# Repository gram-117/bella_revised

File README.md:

# bella

KICAD files + LTspice simulation for PMT driver circuit
tested and working

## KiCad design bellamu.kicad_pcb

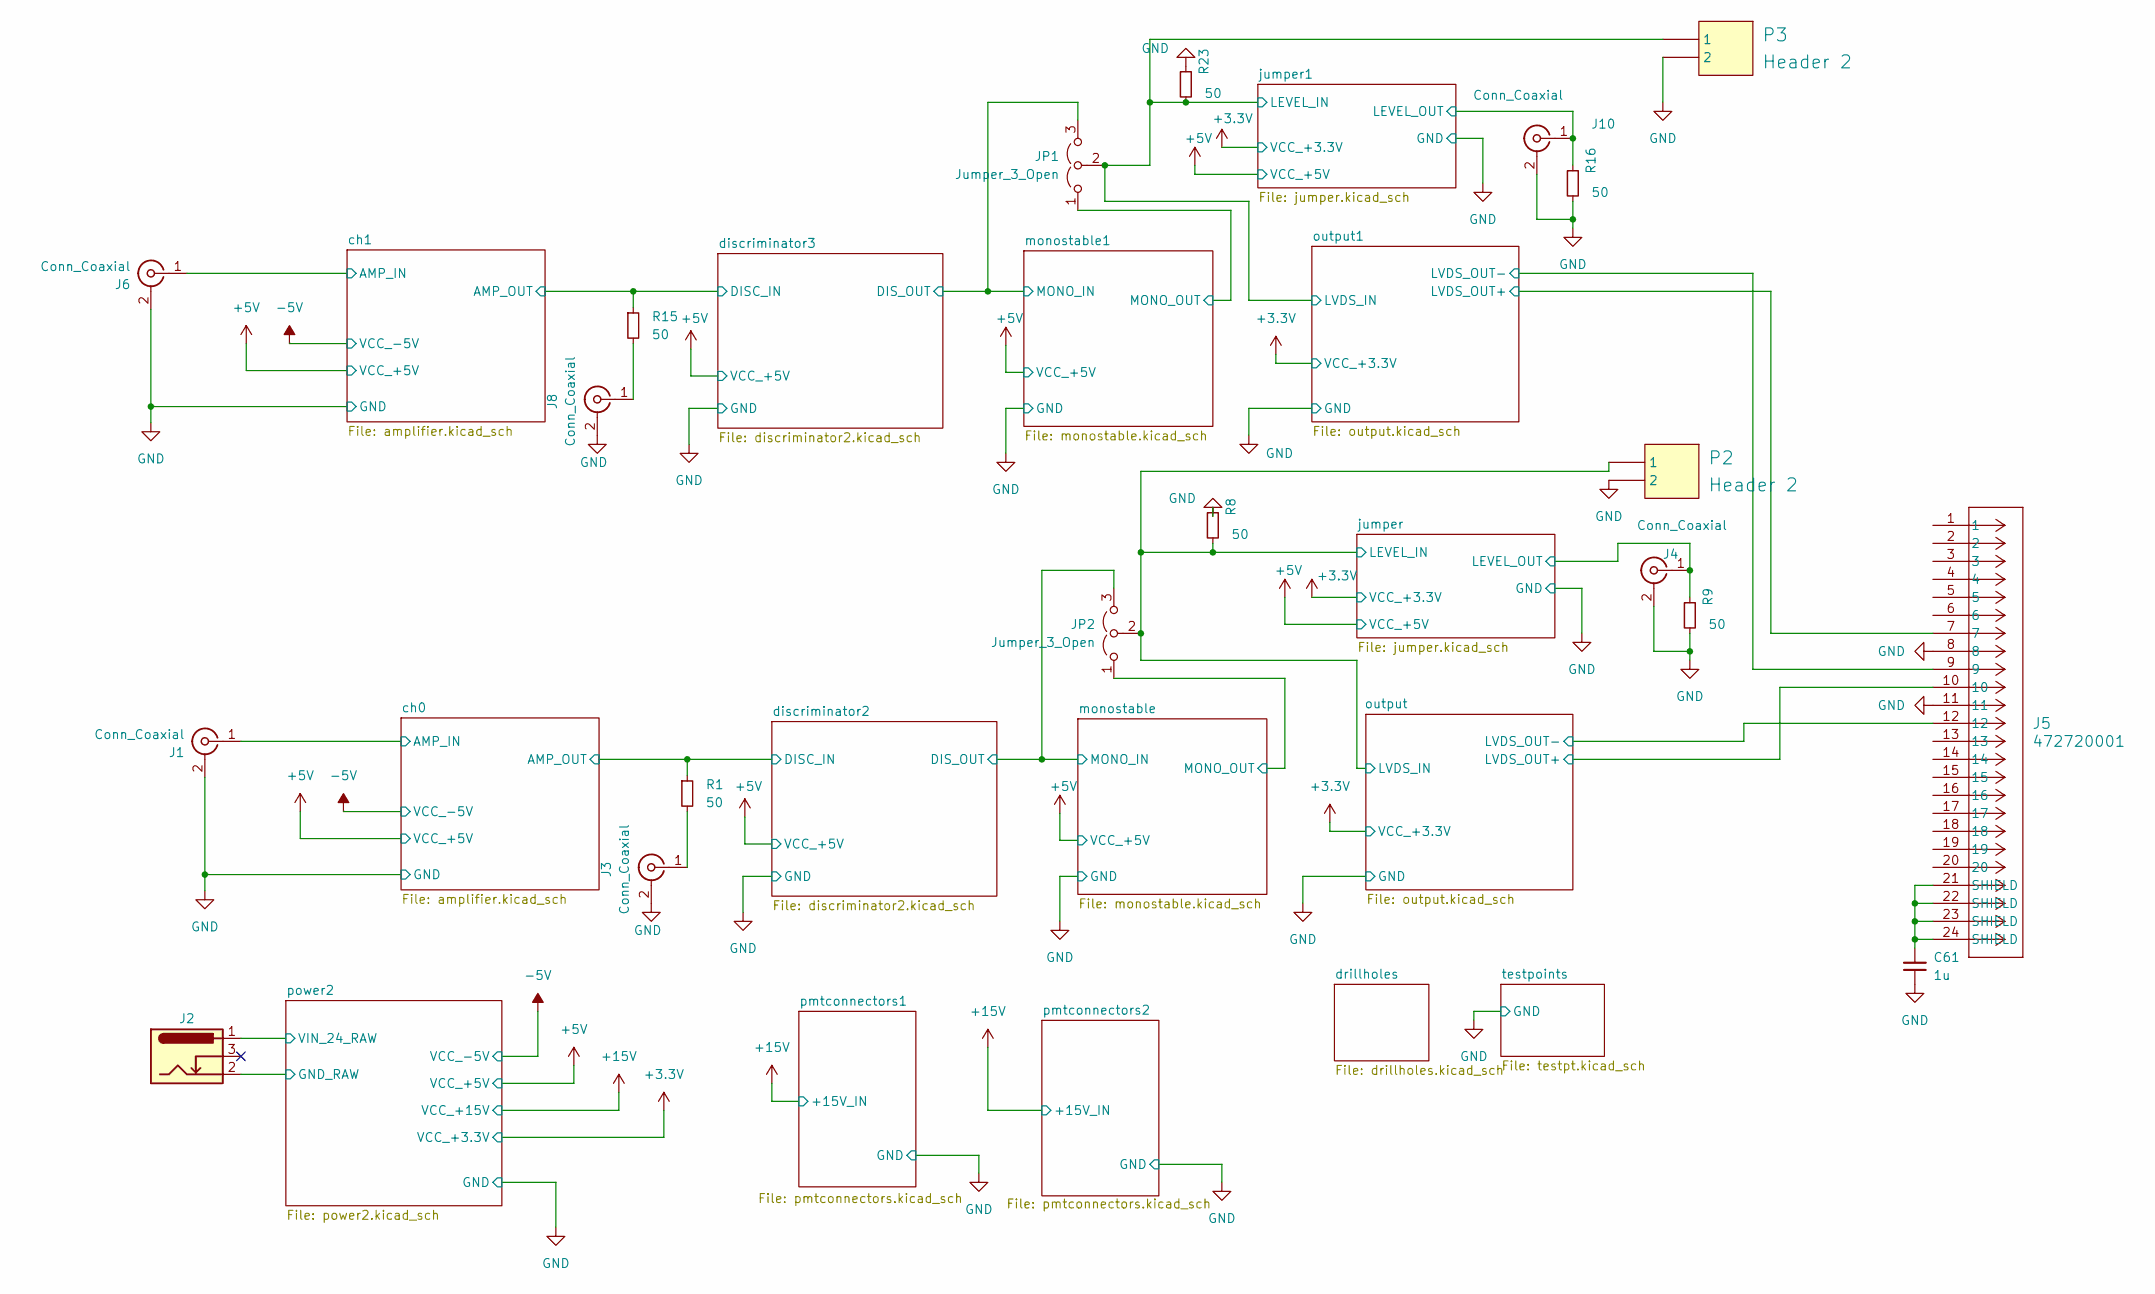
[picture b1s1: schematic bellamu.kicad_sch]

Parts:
C61: 1u; C_0603_1608Metric
J1, J3, J4, J6, J8, J10: Conn_Coaxial; EPB00250NTN
J2: Barrel_Jack_Switch_Pin3Ring; PJ-102AH
J5: 472720001; CONN_47272-0001_MOL
JP1, JP2: Jumper_3_Open; SolderJumper-3_P1.3mm_Open_Pad1.0x1.5mm
P2, P3: Header 2; PinSocket_1x02_P2.54mm_Vertical
R1, R8, R9, R15, R16, R23: 50; R_0805_2012Metric

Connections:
/ch0/AMP_IN: J1.1 (In); also elsewhere on the board
/ch0/AMP_OUT: R1.1; also elsewhere on the board
/ch1/AMP_IN: J6.1 (In); also elsewhere on the board
/ch1/AMP_OUT: R15.1; also elsewhere on the board
/discriminator2/DIS_OUT: JP2.3 (B); also elsewhere on the board
/discriminator3/DIS_OUT: JP1.3 (B); also elsewhere on the board
/jumper1/LEVEL_IN: JP1.2 (C), P3.1, R23.2; also elsewhere on the board
/jumper1/LEVEL_OUT: J10.1 (In), R16.1; also elsewhere on the board
/jumper/LEVEL_IN: JP2.2 (C), P2.1, R8.2; also elsewhere on the board
/jumper/LEVEL_OUT: J4.1 (In), R9.1; also elsewhere on the board
/monostable1/MONO_OUT: JP1.1 (A); also elsewhere on the board
/monostable/MONO_OUT: JP2.1 (A); also elsewhere on the board
/output1/LVDS_OUT+: J5.7; also elsewhere on the board
/output1/LVDS_OUT-: J5.9; also elsewhere on the board
/output/LVDS_OUT+: J5.10; also elsewhere on the board
/output/LVDS_OUT-: J5.12; also elsewhere on the board
/power2/GND_RAW: J2.2; also elsewhere on the board
/power2/VIN_24_RAW: J2.1; also elsewhere on the board
unnamed: C61.2, J5.21 (SHIELD), J5.22 (SHIELD), J5.23 (SHIELD), J5.24 (SHIELD)
unnamed: J3.1 (In), R1.2
unnamed: J8.1 (In), R15.2

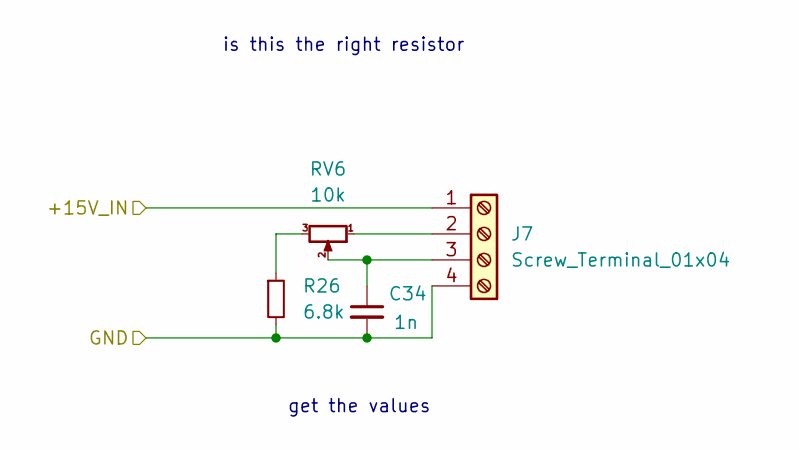
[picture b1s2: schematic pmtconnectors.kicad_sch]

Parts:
C34: 1n; C_0805_2012Metric
J7: Screw_Terminal_01x04; 1725672
R26: 6.8k; R_0805_2012Metric
RV6: 10k; Potentiometer_Bourns_3266W_Vertical

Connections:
+15V: J7.1; also elsewhere on the board
unnamed: J7.2, RV6.1
unnamed: C34.1, J7.3, RV6.2
unnamed: R26.1, RV6.3

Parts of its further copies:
C40: 1n; C_0805_2012Metric
J9: Screw_Terminal_01x04; 1725672
R29: 6.8k; R_0805_2012Metric
RV5: 10k; Potentiometer_Bourns_3266W_Vertical

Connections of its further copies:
+15V: J9.1; also elsewhere on the board
unnamed: J9.2, RV5.1
unnamed: C40.1, J9.3, RV5.2
unnamed: R29.1, RV5.3

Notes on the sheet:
is this the right resistor
get the values

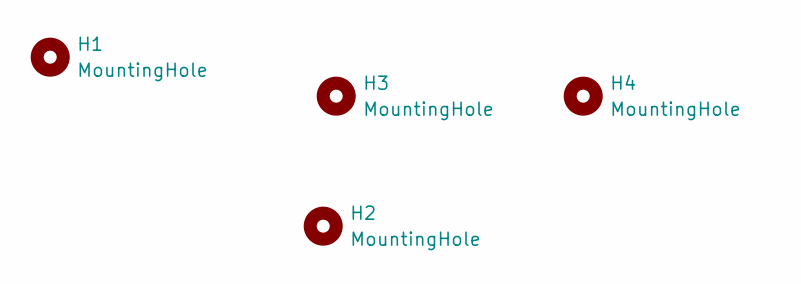
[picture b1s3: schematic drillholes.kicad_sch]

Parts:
H1, H2, H3, H4: MountingHole; MountingHole_2.5mm

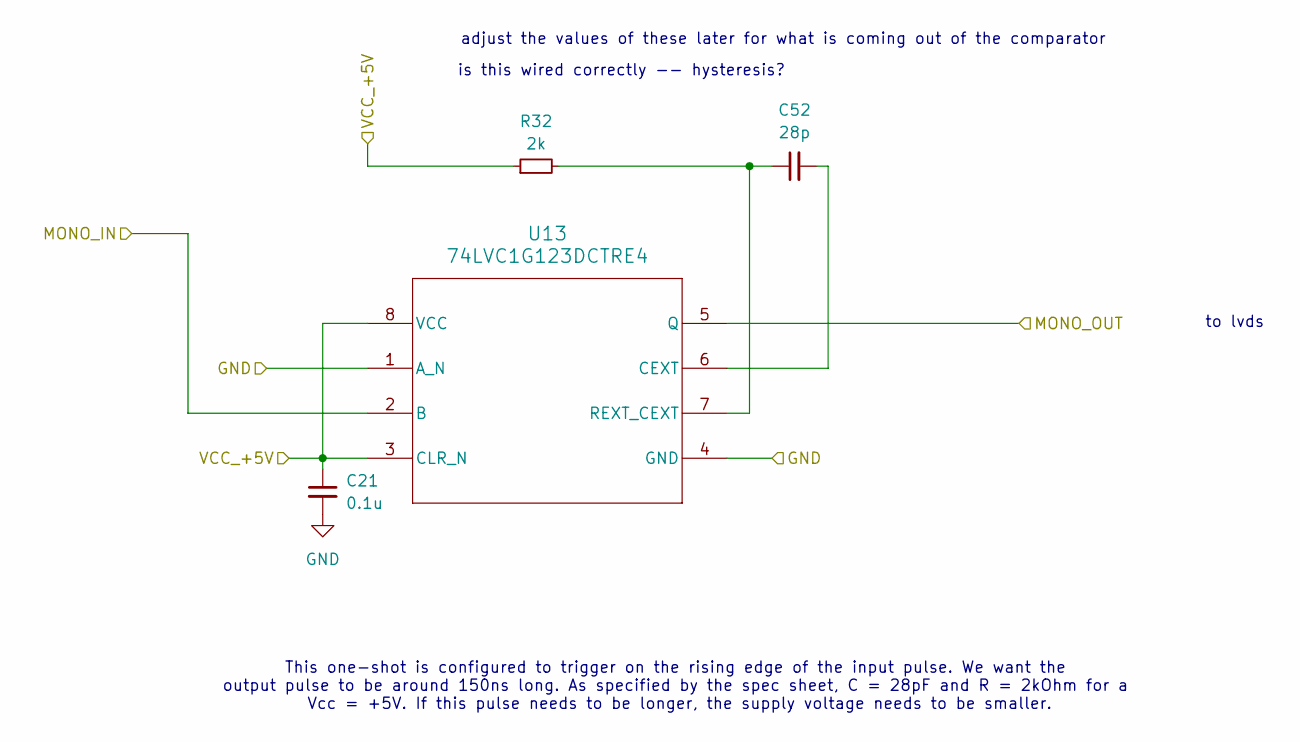
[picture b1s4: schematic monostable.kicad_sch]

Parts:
C21: 0.1u; C_0603_1608Metric
C52: 28p; C_0805_2012Metric
R32: 2k; R_0805_2012Metric
U13: 74LVC1G123DCTRE4; DCT0008A_L

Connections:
+5V: C21.1, R32.1, U13.3 (CLR_N), U13.8 (VCC); also elsewhere on the board
/discriminator2/DIS_OUT: U13.2 (B); also elsewhere on the board
/monostable/MONO_OUT: U13.5 (Q); also elsewhere on the board
unnamed: C52.2, U13.6 (CEXT)
unnamed: C52.1, R32.2, U13.7 (REXT_CEXT)

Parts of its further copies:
C53: 0.1u; C_0603_1608Metric
C54: 28p; C_0805_2012Metric
R33: 2k; R_0805_2012Metric
U15: 74LVC1G123DCTRE4; DCT0008A_L

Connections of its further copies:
+5V: C53.1, R33.1, U15.3 (CLR_N), U15.8 (VCC); also elsewhere on the board
/discriminator3/DIS_OUT: U15.2 (B); also elsewhere on the board
/monostable1/MONO_OUT: U15.5 (Q); also elsewhere on the board
unnamed: C54.2, U15.6 (CEXT)
unnamed: C54.1, R33.2, U15.7 (REXT_CEXT)

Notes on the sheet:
adjust the values of these later for what is coming out of the comparator
This one-shot is configured to trigger on the rising edge of the input pulse. We want the output pulse to be around 150ns long. As specified by the spec sheet, C = 28pF and R = 2kOhm for a Vcc = +5V. If this pulse needs to be longer, the supply voltage needs to be smaller.
is this wired correctly -- hysteresis?
to lvds

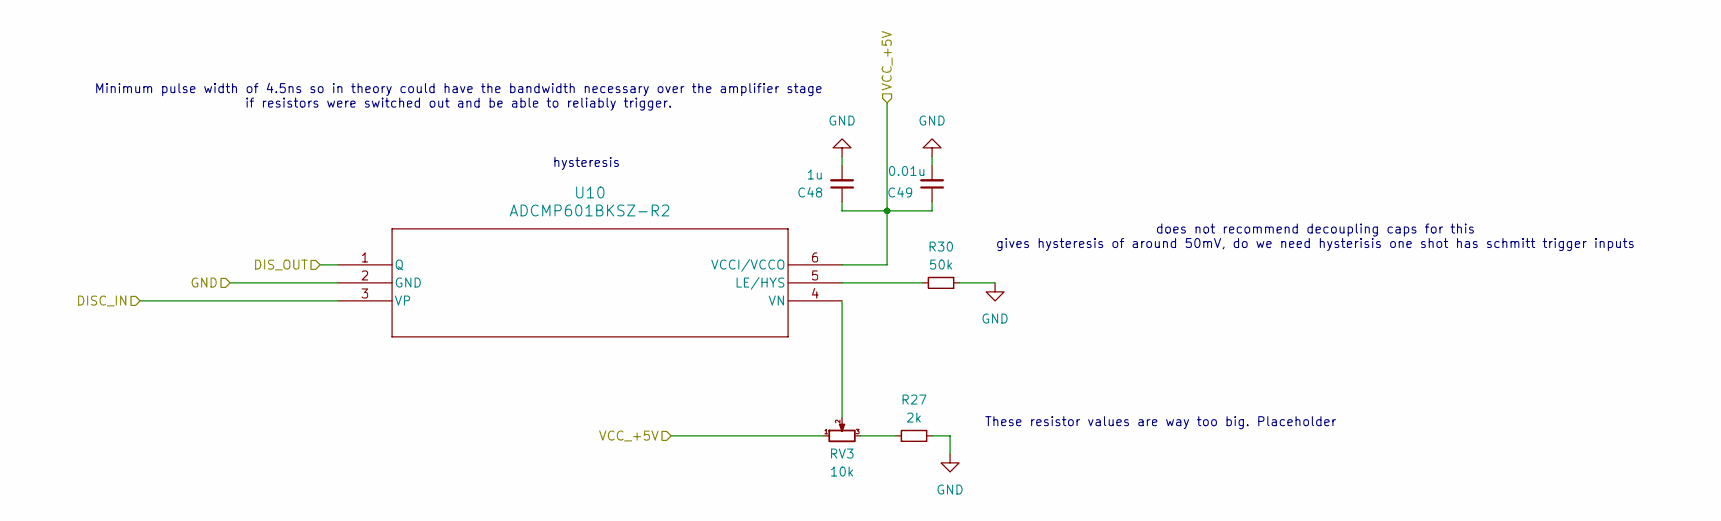
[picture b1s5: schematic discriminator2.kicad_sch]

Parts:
C48: 1u; C_0603_1608Metric
C49: 0.01u; C_0603_1608Metric
R27: 2k; R_0805_2012Metric
R30: 50k; R_0805_2012Metric
RV3: 10k; Potentiometer_Bourns_3266W_Vertical
U10: ADCMP601BKSZ-R2; KS_6_ADI-M

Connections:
+5V: C48.1, C49.1, RV3.1, U10.6 (VCCI/VCCO); also elsewhere on the board
/ch1/AMP_OUT: U10.3 (VP); also elsewhere on the board
/discriminator3/DIS_OUT: U10.1 (Q); also elsewhere on the board
unnamed: R27.1, RV3.3
unnamed: R30.2, U10.5 (LE/HYS)
unnamed: RV3.2, U10.4 (VN)

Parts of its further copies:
C18: 0.01u; C_0603_1608Metric
C19: 1u; C_0603_1608Metric
R14: 50k; R_0805_2012Metric
R31: 2k; R_0805_2012Metric
RV4: 10k; Potentiometer_Bourns_3266W_Vertical
U12: ADCMP601BKSZ-R2; KS_6_ADI-M

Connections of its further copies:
+5V: C18.1, C19.1, RV4.1, U12.6 (VCCI/VCCO); also elsewhere on the board
/ch0/AMP_OUT: U12.3 (VP); also elsewhere on the board
/discriminator2/DIS_OUT: U12.1 (Q); also elsewhere on the board
unnamed: R31.1, RV4.3
unnamed: R14.2, U12.5 (LE/HYS)
unnamed: RV4.2, U12.4 (VN)

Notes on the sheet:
Minimum pulse width of 4.5ns so in theory could have the bandwidth necessary over the amplifier stage if resistors were switched out and be able to reliably trigger.
does not recommend decoupling caps for this gives hysteresis of around 50mV, do we need hysterisis one shot has schmitt trigger inputs
These resistor values are way too big. Placeholder
hysteresis

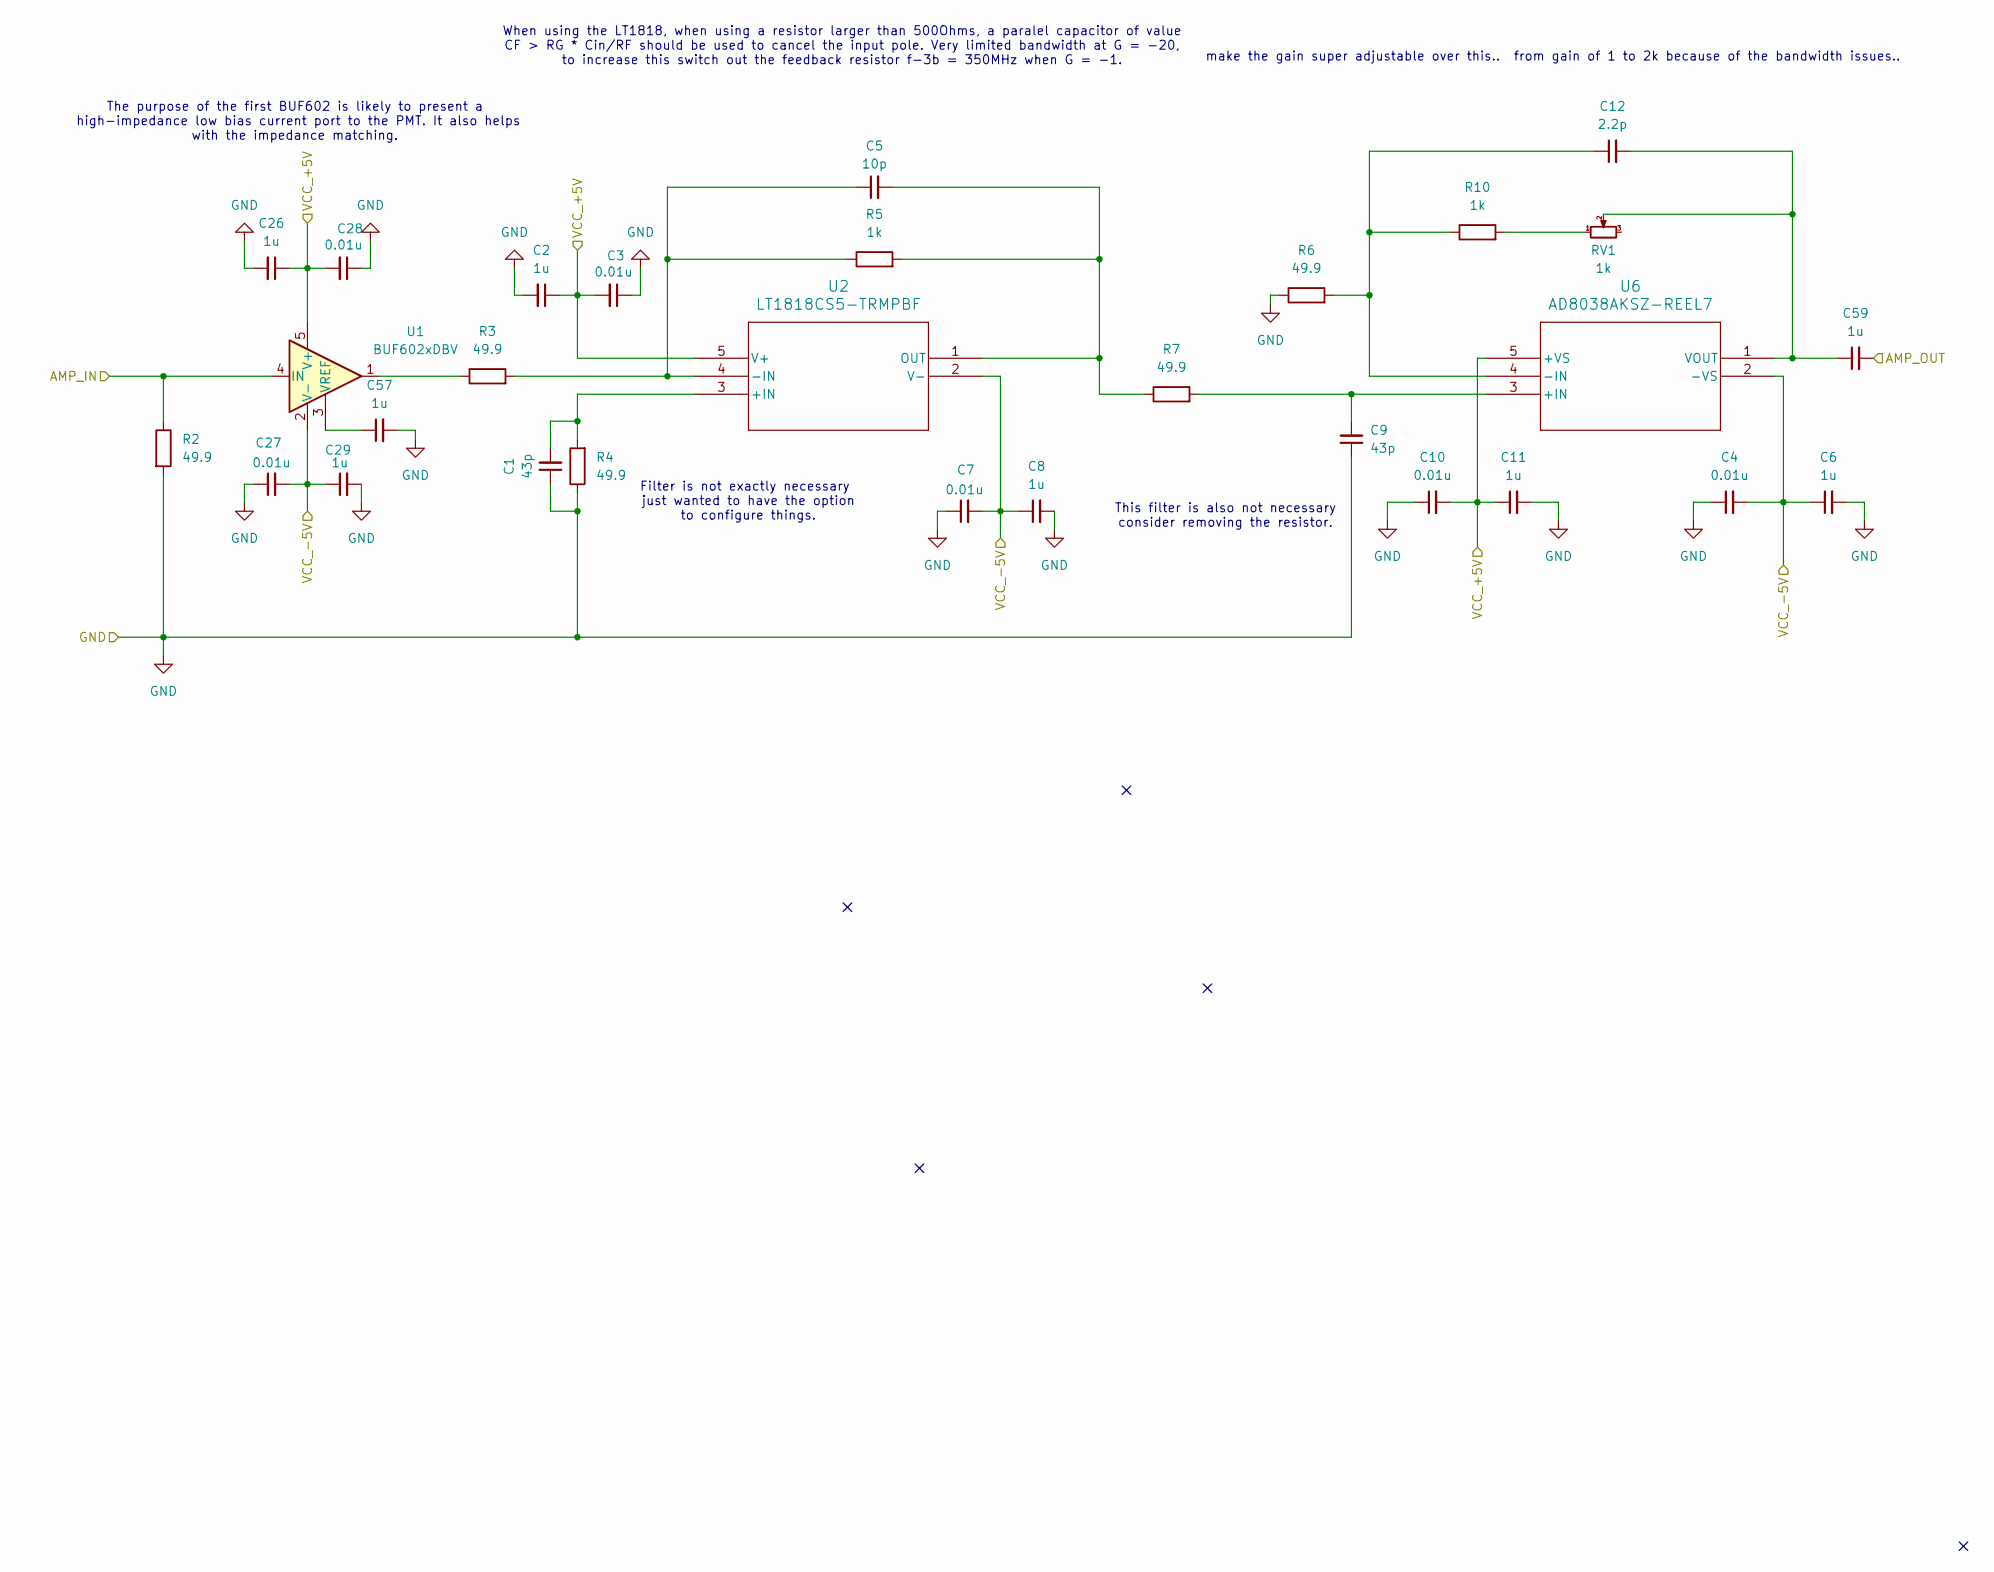
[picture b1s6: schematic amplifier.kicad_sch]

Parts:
C1: 43p; C_0805_2012Metric_Pad1.18x1.45mm_HandSolder
C2, C6, C8, C11, C26, C29, C57: 1u; C_0603_1608Metric
C3, C4, C7, C10, C27, C28: 0.01u; C_0603_1608Metric
C5: 10p; C_0805_2012Metric
C9: 43p; C_0805_2012Metric
C12: 2.2p; C_0805_2012Metric
C59: 1u; C_0805_2012Metric
R2, R3, R4, R6, R7: 49.9; R_0805_2012Metric
R5, R10: 1k; R_0805_2012Metric
RV1: 1k; Potentiometer_Bourns_3266W_Vertical
U1: BUF602xDBV; SOT-23-5
U2: LT1818CS5-TRMPBF; S_5_ADI
U6: AD8038AKSZ-REEL7; KS_5_ADI-M

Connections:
+5V: C2.1, C3.2, C10.2, C11.1, C26.1, C28.2, U1.5 (V+), U2.5 (V+), U6.5 (+VS); also elsewhere on the board
-5V: C4.2, C6.1, C7.2, C8.1, C27.2, C29.1, U1.2 (V-), U2.2 (V-), U6.2 (-VS); also elsewhere on the board
/ch0/AMP_IN: R2.1, U1.4 (IN); also elsewhere on the board
/ch0/AMP_OUT: C59.2; also elsewhere on the board
unnamed: R3.1, U1.1
unnamed: R10.2, RV1.1
unnamed: C57.1, U1.3 (VREF)
unnamed: C1.2, R4.2, U2.3 (+IN)
unnamed: C5.1, R3.2, R5.1, U2.4 (-IN)
unnamed: C5.2, R5.2, R7.1, U2.1 (OUT)
unnamed: C9.2, R7.2, U6.3 (+IN)
unnamed: C12.1, R6.2, R10.1, U6.4 (-IN)
unnamed: C12.2, C59.1, RV1.2, U6.1 (VOUT)

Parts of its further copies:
C30, C33, C36, C41, C44, C47, C58: 1u; C_0603_1608Metric
C31, C32, C37, C39, C43, C46: 0.01u; C_0603_1608Metric
C35: 43p; C_0805_2012Metric_Pad1.18x1.45mm_HandSolder
C38: 10p; C_0805_2012Metric
C42: 43p; C_0805_2012Metric
C45: 2.2p; C_0805_2012Metric
C60: 1u; C_0805_2012Metric
R17, R18, R19, R21, R22: 49.9; R_0805_2012Metric
R20, R25: 1k; R_0805_2012Metric
RV2: 1k; Potentiometer_Bourns_3266W_Vertical
U7: BUF602xDBV; SOT-23-5
U8: LT1818CS5-TRMPBF; S_5_ADI
U9: AD8038AKSZ-REEL7; KS_5_ADI-M

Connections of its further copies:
+5V: C30.1, C32.2, C36.1, C37.2, C43.2, C44.1, U7.5 (V+), U8.5 (V+), U9.5 (+VS); also elsewhere on the board
-5V: C31.2, C33.1, C39.2, C41.1, C46.2, C47.1, U7.2 (V-), U8.2 (V-), U9.2 (-VS); also elsewhere on the board
/ch1/AMP_IN: R17.1, U7.4 (IN); also elsewhere on the board
/ch1/AMP_OUT: C60.2; also elsewhere on the board
unnamed: R18.1, U7.1
unnamed: R25.2, RV2.1
unnamed: C58.1, U7.3 (VREF)
unnamed: C35.2, R19.2, U8.3 (+IN)
unnamed: C38.1, R18.2, R20.1, U8.4 (-IN)
unnamed: C38.2, R20.2, R21.1, U8.1 (OUT)
unnamed: C42.2, R21.2, U9.3 (+IN)
unnamed: C45.1, R22.2, R25.1, U9.4 (-IN)
unnamed: C45.2, C60.1, RV2.2, U9.1 (VOUT)

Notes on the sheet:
make the gain super adjustable over this.. from gain of 1 to 2k because of the bandwidth issues..
The purpose of the first BUF602 is likely to present a high-impedance low bias current port to the PMT. It also helps with the impedance matching.
When using the LT1818, when using a resistor larger than 500Ohms, a paralel capacitor of value CF > RG * Cin/RF should be used to cancel the input pole. Very limited bandwidth at G = -20, to increase this switch out the feedback resistor f-3b = 350MHz when G = -1.
Filter is not exactly necessary just wanted to have the option to configure things.
This filter is also not necessary consider removing the resistor.

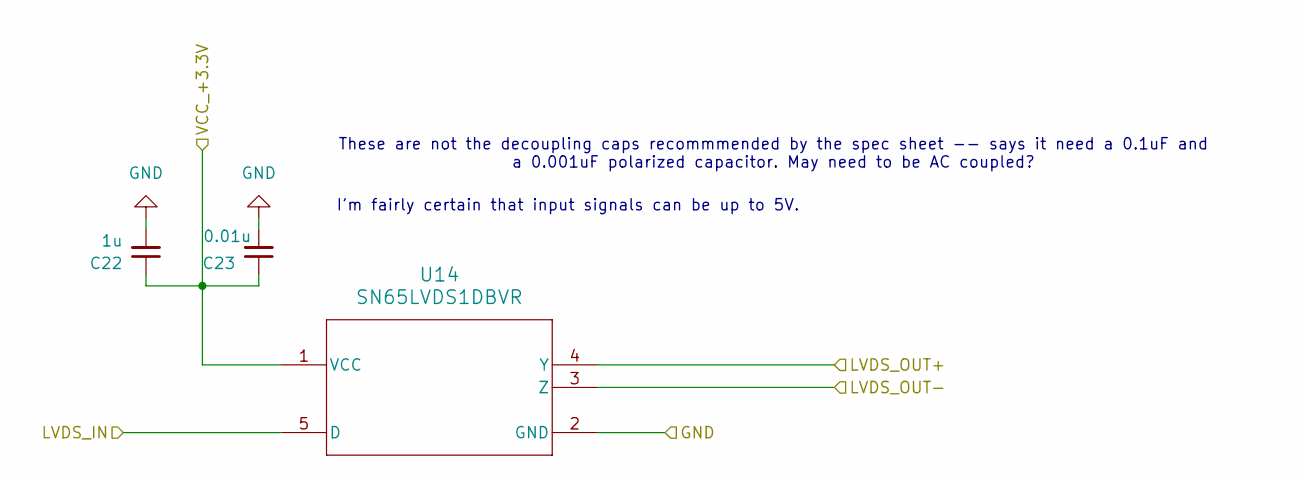
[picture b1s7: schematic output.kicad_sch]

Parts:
C22: 1u; C_0603_1608Metric
C23: 0.01u; C_0603_1608Metric
U14: SN65LVDS1DBVR; DBV0005A_L

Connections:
+3.3V: C22.1, C23.1, U14.1 (VCC); also elsewhere on the board
/jumper/LEVEL_IN: U14.5 (D); also elsewhere on the board
/output/LVDS_OUT+: U14.4 (Y); also elsewhere on the board
/output/LVDS_OUT-: U14.3 (Z); also elsewhere on the board

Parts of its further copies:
C55: 1u; C_0603_1608Metric
C56: 0.01u; C_0603_1608Metric
U16: SN65LVDS1DBVR; DBV0005A_L

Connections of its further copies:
+3.3V: C55.1, C56.1, U16.1 (VCC); also elsewhere on the board
/jumper1/LEVEL_IN: U16.5 (D); also elsewhere on the board
/output1/LVDS_OUT+: U16.4 (Y); also elsewhere on the board
/output1/LVDS_OUT-: U16.3 (Z); also elsewhere on the board

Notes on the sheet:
These are not the decoupling caps recommmended by the spec sheet -- says it need a 0.1uF and a 0.001uF polarized capacitor. May need to be AC coupled?
I'm fairly certain that input signals can be up to 5V.

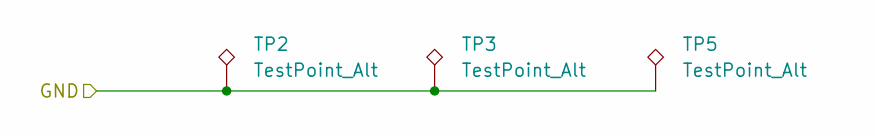
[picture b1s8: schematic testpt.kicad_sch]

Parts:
TP2, TP3, TP5: TestPoint_Alt; TestPoint_Loop_D2.54mm_Drill1.5mm_Beaded

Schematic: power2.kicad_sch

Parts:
C13: 0.47u; C_0805_2012Metric
C14, C15: 10u; CAPC3225X280N
C16, C17: 1n; CAPC4520X200N
C20: 33u; C_0805_2012Metric
D1, D2, D3: LED; LED_0805_2012Metric
L1, L2: 10u; IND_TCK-047_TRP
P1, P4, P5: Header 4; PinHeader_1x04_P2.54mm_Vertical
P6: Header 2; PinHeader_1x02_P2.54mm_Vertical
PS1: TMR_6-2413WIR; TMR62423; PARTREV November 16, 2023
R11: 680; R_0805_2012Metric
R12, R13: 150; R_0805_2012Metric
R24, R28: 10k; R_0805_2012Metric
S1, S2: BB16AH-FA; KSA_Tactile_SPST; Mouser Part Number 633-BB16AH-FA
TP1: TestPoint_Alt; TestPoint_THTPad_D2.5mm_Drill1.2mm
U3: TMR 6-2421WIR; TMR62423
U4: LM3940IMP-3.3; MP04A

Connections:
+3.3V: C20.1, P6.1, U4.3 (OUT); also elsewhere on the board
+5V: C13.1, P4.1, P4.2, R12.1, U3.6 (+VOUT), U4.1 (IN); also elsewhere on the board
+15V: P5.1, P5.2, PS1.6 (+VOUT), R11.2; also elsewhere on the board
-5V: C17.2, P1.1, P1.2, R13.1, U3.8 (-VOUT); also elsewhere on the board
/power2/GND_RAW: C14.1, C15.1, C16.1, C17.1, PS1.1 (-VIN(GND)), TP1.1, U3.1 (-VIN(GND)); also elsewhere on the board
/power2/VIN_24_RAW: C14.2, C15.2, L1.2, L2.2; also elsewhere on the board
unnamed: D1.2 (A), R11.1
unnamed: D2.2 (A), R12.2
unnamed: D3.1 (K), R13.2
unnamed: L2.1, PS1.2 (+VIN(VCC)), S1.1 (NO)
unnamed: PS1.3 (REMOTE), R28.1
unnamed: R28.2, S1.2 (COM)
unnamed: R24.2, S2.2 (COM)
unnamed: L1.1, S2.1 (NO), U3.2 (+VIN(VCC))
unnamed: R24.1, U3.3 (REMOTE)

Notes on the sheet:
add remote control
CASE
i believe case is no connect but i don't know
no fuse
case may need to be connected to ground or to ps idk
check footprints here
tvs diode needed?
is this being pulled down in the correct way

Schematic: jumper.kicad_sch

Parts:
C50, C51: 0.1u; C_0603_1608Metric
U11: SN74LVC1T45DBV; SOT-23-6

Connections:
+3.3V: C51.1, U11.1 (VCCA); also elsewhere on the board
+5V: C50.1, U11.6 (VCCB); also elsewhere on the board
/jumper1/LEVEL_IN: U11.4 (B); also elsewhere on the board
/jumper1/LEVEL_OUT: U11.3 (A); also elsewhere on the board

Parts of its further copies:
C24, C25: 0.1u; C_0603_1608Metric
U5: SN74LVC1T45DBV; SOT-23-6

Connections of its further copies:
+3.3V: C25.1, U5.1 (VCCA); also elsewhere on the board
+5V: C24.1, U5.6 (VCCB); also elsewhere on the board
/jumper/LEVEL_IN: U5.4 (B); also elsewhere on the board
/jumper/LEVEL_OUT: U5.3 (A); also elsewhere on the board

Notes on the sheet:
Direction from B -> A, input DIR driven L

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
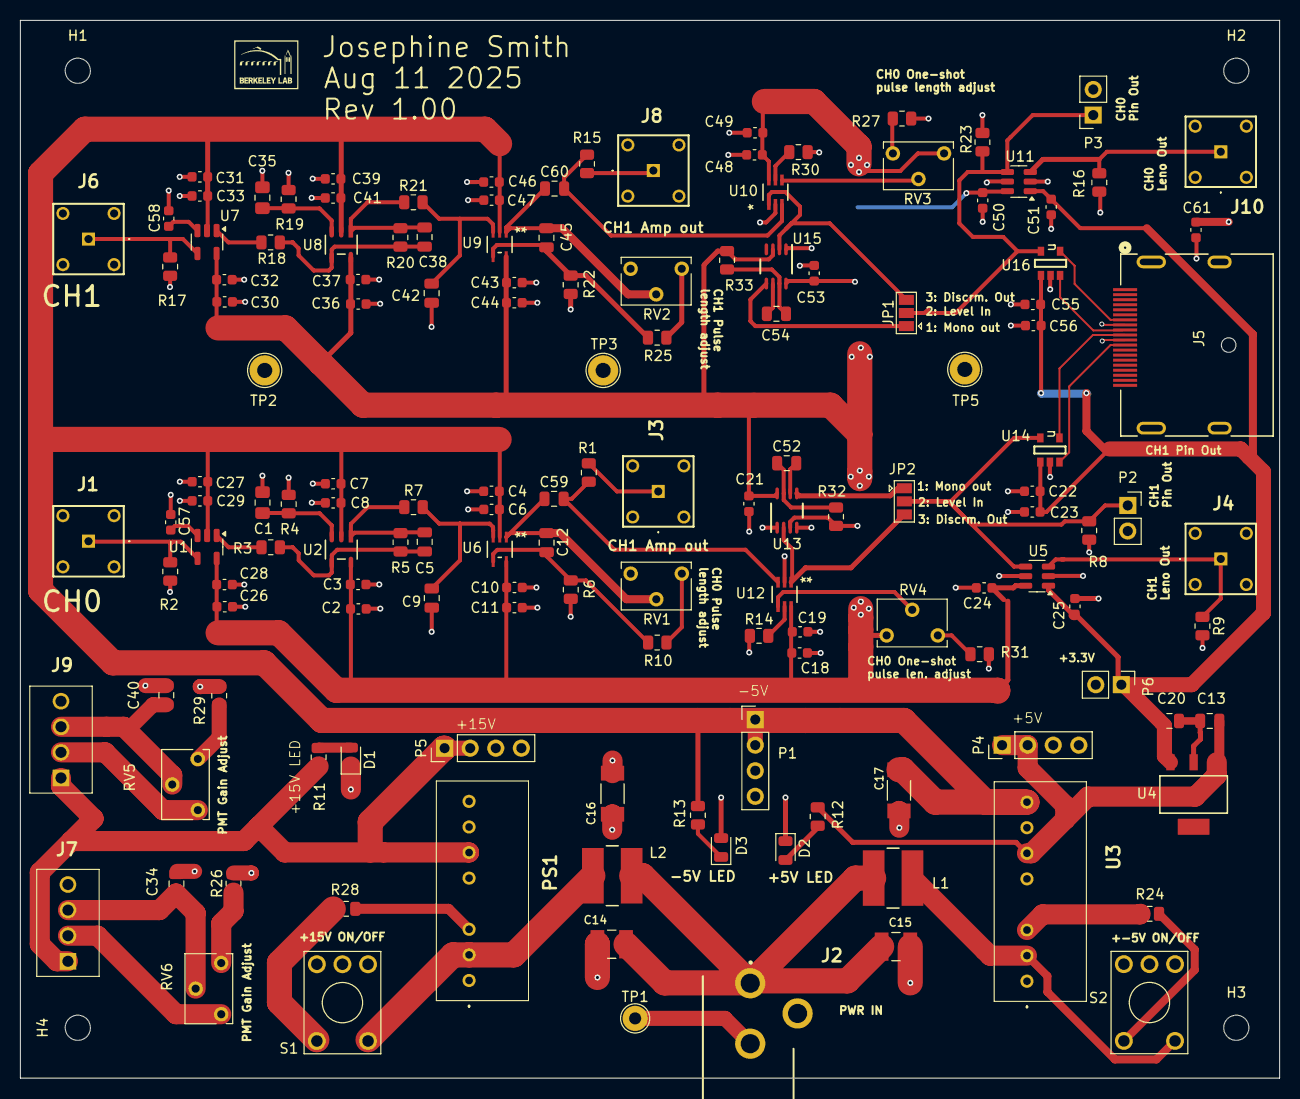
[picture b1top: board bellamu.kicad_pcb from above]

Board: 2 copper layers, 125.0 x 105.0 mm, 150 parts (0 on the bottom side), 70 nets.

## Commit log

2025-10-18 kicad
2025-10-18 edits
2025-11-25 Remove duplicate header from README.md
2025-11-25 Rename amplifier.kicad_sch to schFiles/amplifier.kicad_sch
2025-11-25 Rename testpt.kicad_sch to schFiles/testpt.kicad_sch
2025-11-25 Rename monostable.kicad_sch to schFiles/monostable.kicad_sch
2025-11-25 Rename output.kicad_sch to schFiles/output.kicad_sch
2025-11-25 Rename pmtconnectors.kicad_sch to schFiles/pmtconnectors.kicad_sch
2025-11-25 Rename bellamu.kicad_sch to schFiles/bellamu.kicad_sch
2025-11-25 Rename drillholes.kicad_sch to schFiles/drillholes.kicad_sch
2025-11-25 Rename discriminator.kicad_sch to schFiles/discriminator.kicad_sch
2025-12-19 revised pcb and schematics
2025-12-19 docs
